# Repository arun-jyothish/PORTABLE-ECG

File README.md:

# PORTABLE-ECG
A Handheld ECG Machine with Mobile phone and Laptop interface. Cardiac condition prediction using ML

[jump to README 2](src/README.md)

[variable link][var link]
LOCK

[var link]: https://GOOGLE.COM 

|part name|LCSC PART NO|LINK|
|-----|-----|----|
|OLED| 	C2890600|https://lcsc.com/product-detail/span-style-background-color-ff0-OLED-span-Displays-Modules_Shenzhen-Allvision-Tech-N096-2864TMBEG0-H30_C2890600.html|
|RESISTOR|
|CAPACITOR|
|TYPEC CONN|
hello world
<br>

[![Contributors][Contributors-shield]][Contributors-url]

<br>

## P-ECG MACHINE

In the prediction feature, patient's ECG signal is compared with various cardio gram.
as the processing result the machine filter out many heart disease and predicts the most probable disease that should affect the person's life'

## BLOCK DIAGRAM
~~~mermaid

graph TD
 
    UART-->PWR
    PWR[USB PORT]-->CHR[CHARGING CIRCUIT]
    CHR-->BAT[BATTERY 3.7 LI-ION]
    RGL[POWER REGULATOR]-.->|3.3 VOLT|OLED[OLED 128*64]
    CHR-->RGL
    BAT-->RGL
    RGL-.->|3.7 VOLT|UC 
    UC{MICROCONTROLLER}-->OLED
   
    UC-->UART[USB TO TTL CONVERTER]
    PWR-.->EXT[COMPUTER]
    PWR-.->EXT2[MOBILE]
    probe[/PROBE/]-->|DATA|INS
    RGL-.->INS
    RA((RA))-->probe
    RL((RL))-->probe
    LA((LA))-->probe
    INS[INSTRUMENTATION AMPLIFIER] --->|ANALOG DATA| UC
~~~

~~~mermaid
graph TD 

   I((IDEATION)) --> Q[PREPARE FAQ] 
    I --> D[CONSTRAINTS IN NEW IMPLEMENTATION]
    D-->M[ MEASURES TAKEN ]
    EX[IDENTIFYING EXISTING TECHNOLOGY]-->I
    FL[IDENTIFYING LIMITATIONS]-->I
    
~~~
~~~mermaid
graph TD
    H[COMPONENTS SELECTION]-->SCH[PREPARE SCHEMATICS]
    SCH-->PCB[DESIGN PCB LAYOUT]
   DSN[CHASY DESIGN]-->TST[TESTING STAGE]
    TST-.->|FAIL|SCH
    TST==>|SUCCESS|FINAL((PRODUCT))
    PCB-->DSN

~~~
[contributors-shield]: https://img.shields.io/github/contributors/Arun-jyothish/PORTABLE-ECG.svg?style=for-the-badge
[Contributors-url]:https://github.com/Arun-jyothish/PORTABLE-ECG/network/members

~~~mermaid

~~~

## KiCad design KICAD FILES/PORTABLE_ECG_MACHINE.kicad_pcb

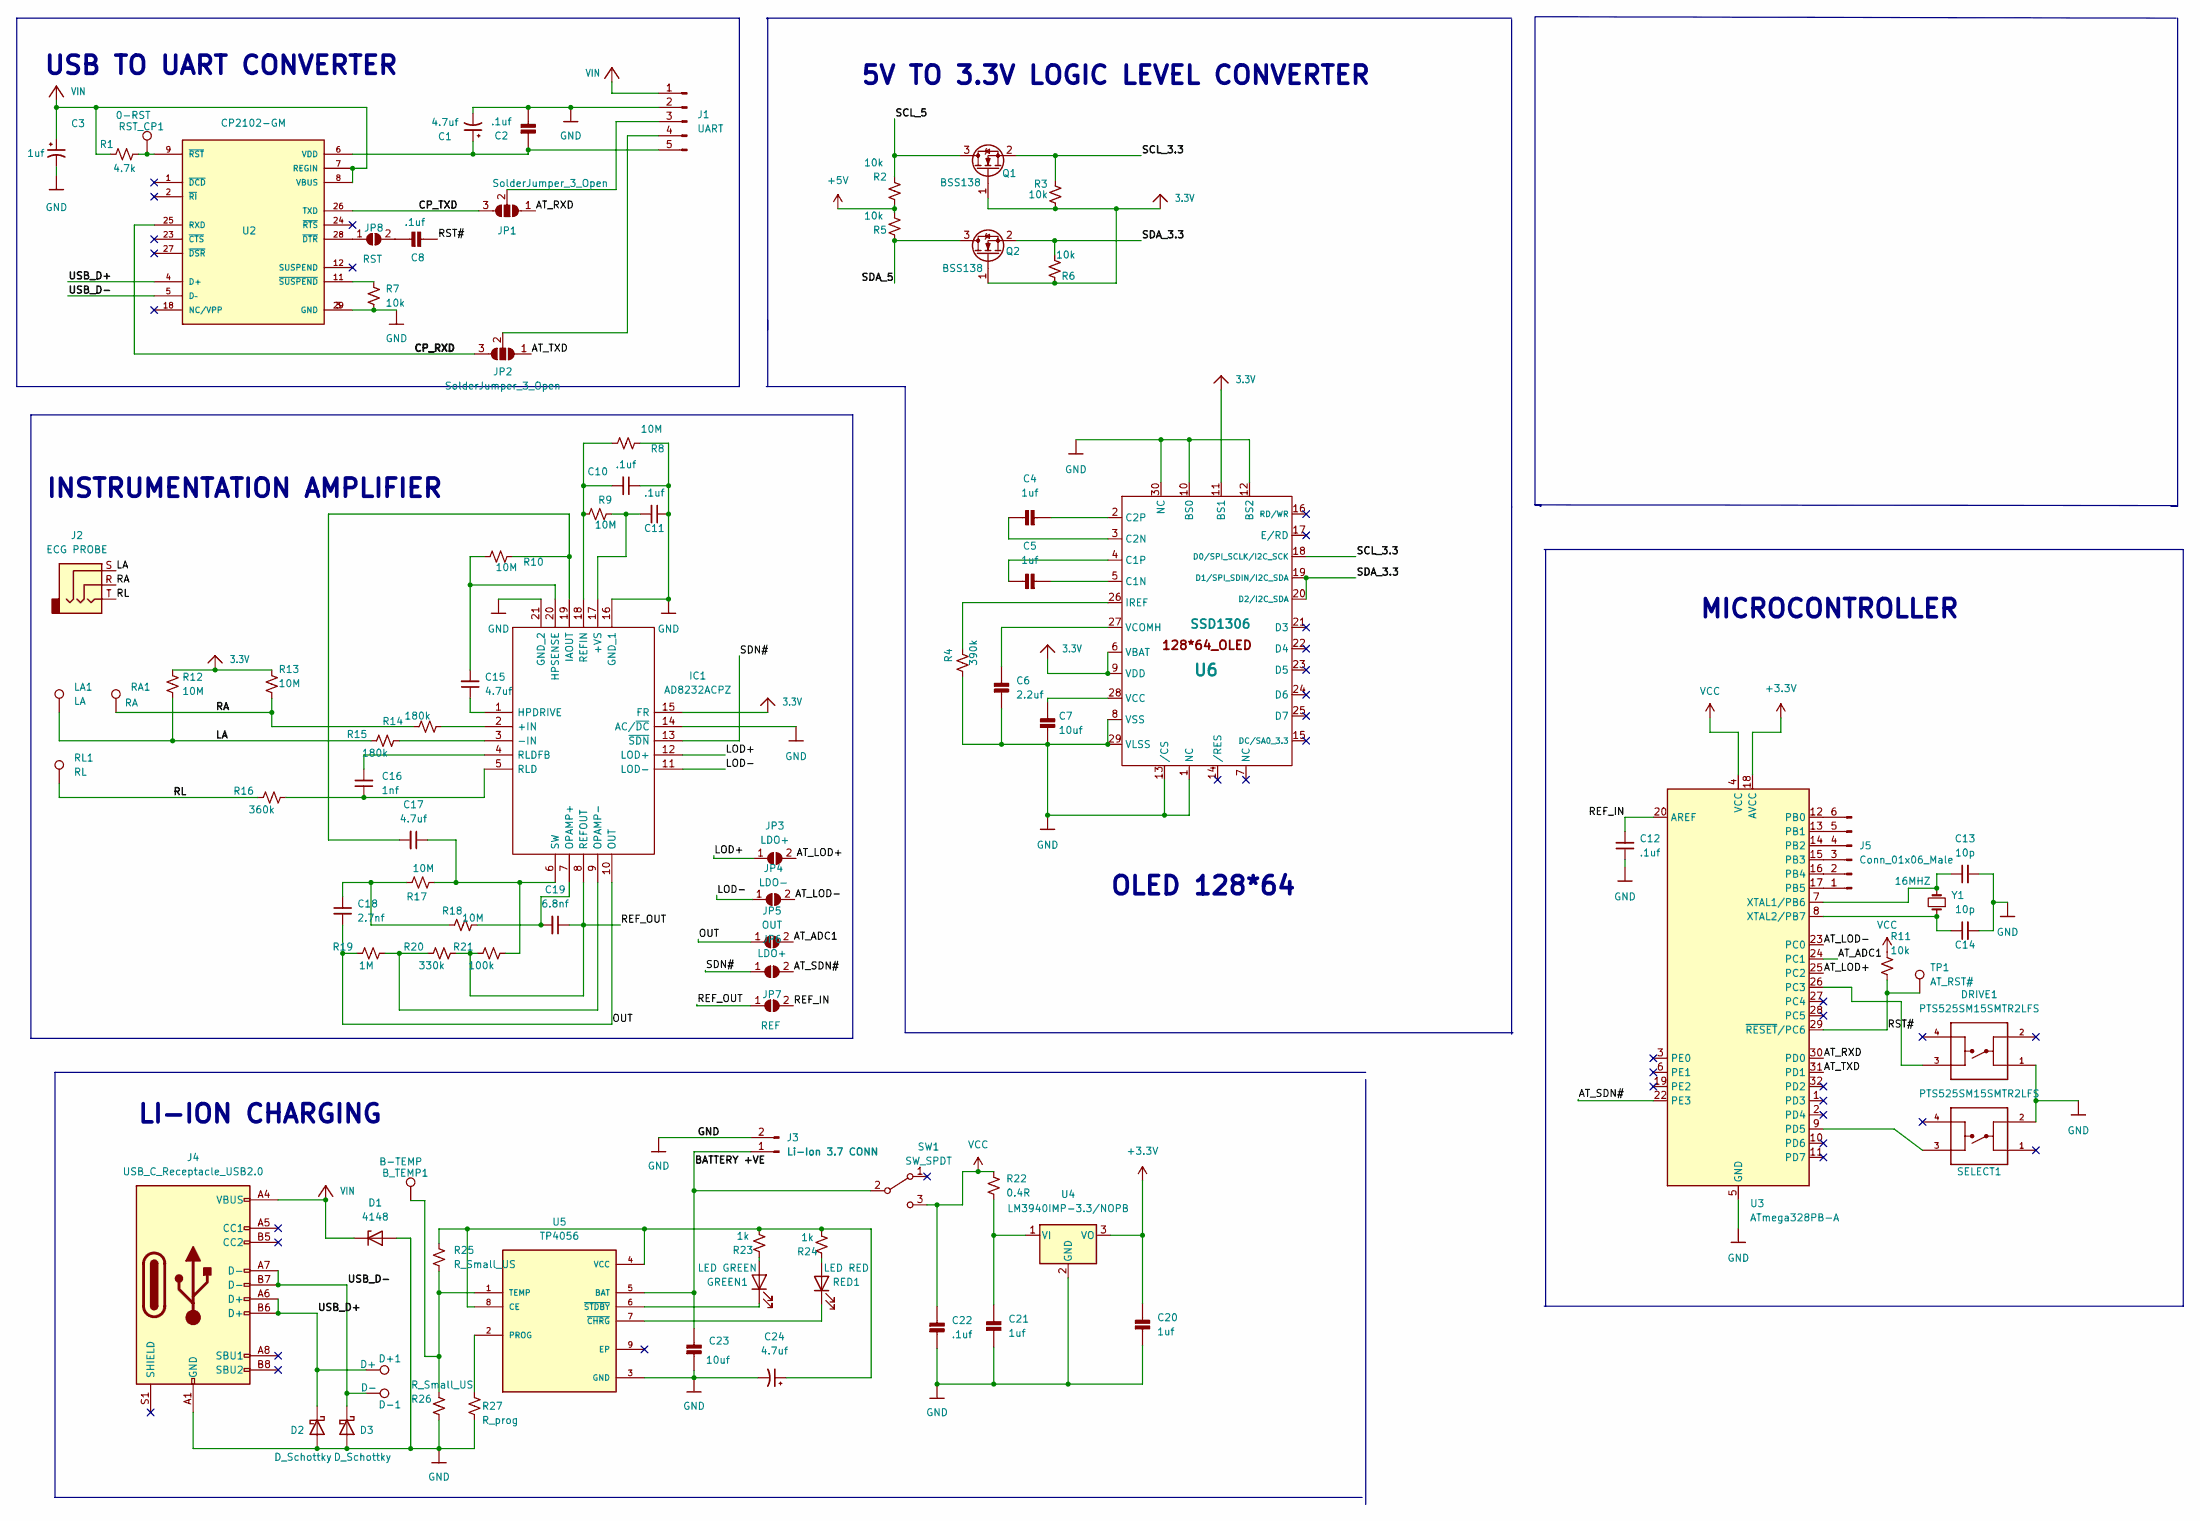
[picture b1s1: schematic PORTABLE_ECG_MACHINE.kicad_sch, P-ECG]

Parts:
B_TEMP1: B-TEMP; TestPoint_Pad_D1.0mm
C1, C15, C17, C24: 4.7uf; C_0603_1608Metric; JLC PCB PART NUMBER C2204347
C2, C8, C10, C11, C12, C22: .1uf; C_0603_1608Metric; JLC PCB PART NUMBER C2237744
C3, C4, C5, C20, C21: 1uf; C_0603_1608Metric; JLC PCB PART NUMBER C2168630
C6: 2.2uf; C_0603_1608Metric; JLC PCB PART NUMBER C2858007
C7, C23: 10uf; C_0603_1608Metric; JLC PCB PART NUMBER C2167337
C13, C14: 10p; C_0603_1608Metric; JLC PCB PART NUMBER C2184695
C16: 1nf; C_0603_1608Metric; JLC PCB PART NUMBER C100040
C18: 2.7nf; C_0603_1608Metric; JLC PCB PART NUMBER C107085
C19: 6.8nf; C_0603_1608Metric; JLC PCB PART NUMBER C2185892
D1: 4148; D_0603_1608Metric; JLC PCB PART NUMBER C109002
D2, D3: D_Schottky; D_0603_1608Metric; JLC PCB PART NUMBER C143772
D+1: D+; TestPoint_Pad_D1.0mm
D-1: D-; TestPoint_Pad_D1.0mm
DRIVE1: PTS525SM15SMTR2LFS; SW_PTS525SM15SMTR2LFS; PARTREV NA; JLC PCB PART NUMBER C221856
GREEN1: LED GREEN; LED_0603_1608Metric; JLC PCB PART NUMBER C2917809
IC1: AD8232ACPZ; QFN50P400X400X80-21N-D; Manufacturer_Part_Number AD8232ACPZ; Mouser Part Number N/A
J1: UART; PinHeader_1x05_P1.00mm_Horizontal
J2: ECG PROBE; Jack_3.5mm_CUI_SJ-3524-SMT_Horizontal; JLC PCB PART NUMBER C2939151
J3: Li-Ion 3.7 CONN; PinHeader_1x02_P1.00mm_Horizontal
J4: USB_C_Receptacle_USB2.0; USB_C_Receptacle_HRO_TYPE-C-31-M-12; JLC PCB PART NUMBER C2927026
J5: Conn_01x06_Male; 6PIN_CONN
JP1, JP2: SolderJumper_3_Open; 3_PIN_SOLDER_JUMPER_SMD
JP3, JP6: LDO+; 2_PIN_SMD_SOLDER_JUMPER
JP4: LDO-; 2_PIN_SMD_SOLDER_JUMPER
JP5: OUT; 2_PIN_SMD_SOLDER_JUMPER
JP7: REF; 2_PIN_SMD_SOLDER_JUMPER
JP8: RST; 2_PIN_SMD_SOLDER_JUMPER
LA1: LA; TestPoint_Pad_D1.0mm
Q1, Q2: BSS138; SOT-23; JLC PCB PART NUMBER C549757
R1: 4.7k; R_0603_1608Metric; JLC PCB PART NUMBER C2907166
R2, R3, R5, R6, R7, R11: 10k; R_0603_1608Metric; JLC PCB PART NUMBER C2930027
R4: 390k; R_0603_1608Metric; JLC PCB PART NUMBER C304747
R8, R9, R10, R12, R13, R17, R18: 10M; R_0603_1608Metric; JLC PCB PART NUMBER C2907090
R14, R15: 180k; R_0603_1608Metric; JLC PCB PART NUMBER C2907090
R16: 360k; R_0603_1608Metric; JLC PCB PART NUMBER C2907090
R19: 1M; R_0603_1608Metric; JLC PCB PART NUMBER C2907115
R20: 330k; R_0603_1608Metric; JLC PCB PART NUMBER C2907151
R21: 100k; R_0603_1608Metric; JLC PCB PART NUMBER C328419
R22: 0.4R; R_0603_1608Metric; JLC PCB PART NUMBER C2907088
R23, R24: 1k; R_0603_1608Metric; JLC PCB PART NUMBER C2913953
R25, R26: R_Small_US; R_0603_1608Metric
R27: R_prog; R_0603_1608Metric
RA1: RA; TestPoint_Pad_D1.0mm
RED1: LED RED; LED_0603_1608Metric; JLC PCB PART NUMBER C2917808
RL1: RL; TestPoint_Pad_D1.0mm
RST_CP1: 0-RST; TestPoint_Pad_D1.0mm
SELECT1: PTS525SM15SMTR2LFS; SW_PTS525SM15SMTR2LFS; PARTREV NA; JLC PCB PART NUMBER C221856
SW1: SW_SPDT; SW_SPDT_PCM12; JLC PCB PART NUMBER C2890358
TP1: AT_RST#; TestPoint_Pad_D1.0mm
U2: CP2102-GM; QFN50P500X500X100-29N; PARTREV 1.8; JLC PCB PART NUMBER C6568
U3: ATmega328PB-A; TQFP-32_7x7mm_P0.8mm; JLC PCB PART NUMBER C194192
U4: LM3940IMP-3.3/NOPB; SOT-223; JLC PCB PART NUMBER C140319
U5: TP4056; SOP127P600X175-9N; JLC PCB PART NUMBER C725790
U6: SSD1306; OLED-128O064D; JLC PCB PART NUMBER C2890600
Y1: 16MHZ; Crystal_SMD_0603-2Pin_6.0x3.5mm; JLC PCB PART NUMBER C112972

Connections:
3.3V: IC1.15 (FR), Q1.1 (G), Q2.1 (G), R3.1, R6.1, R12.1, R13.1, U6.6 (VBAT), U6.9 (VDD), U6.11 (BS1)
+3V3: C20.1, U3.18 (AVCC), U4.3 (VO)
+5V: R2.1, R5.2
/AT_ADC1: JP5.2 (B), U3.24 (PC1)
/AT_LOD+: JP3.2 (B), U3.25 (PC2)
/AT_LOD-: JP4.2 (B), U3.23 (PC0)
/AT_RXD: JP1.1 (A), U3.30 (PD0)
/AT_SDN#: JP6.2 (B), U3.22 (PE3)
/AT_TXD: JP2.1 (A), U3.31 (PD1)
/BATTERY +VE: C23.1, J3.1, SW1.2 (B), U5.5 (BAT)
/CP_RXD: JP2.3 (B), U2.25 (RXD)
/CP_TXD: JP1.3 (B), U2.26 (TXD)
/LA: J2.S, LA1.1, R12.2, R15.1
/LOD+: IC1.12 (LOD+), JP3.1 (A)
/LOD-: IC1.11 (LOD-), JP4.1 (A)
/OUT: C18.1, IC1.10 (OUT), JP5.1 (A), R19.1
/RA: J2.R, R13.2, R14.1, RA1.1
/REF_IN: C12.2, JP7.2 (B), U3.20 (AREF)
/REF_OUT: C19.1, IC1.8 (REFOUT), JP7.1 (A), R20.2, R21.1
/RL: J2.T, R16.1, RL1.1
/RST#: C8.2, R11.2, TP1.1, U3.29 (~RESET/PC6)
/SCL_3.3: Q1.2 (S), R3.2, U6.18 (D0/SPI_SCLK/I2C_SCK)
/SCL_5: Q1.3 (D), R2.2
/SDA_3.3: Q2.2 (S), R6.2, U6.19 (D1/SPI_SDIN/I2C_SDA), U6.20 (D2/I2C_SDA)
/SDA_5: Q2.3 (D), R5.1
/SDN#: IC1.13 (~SDN), JP6.1 (A)
/USB_D+: D2.1 (K), D+1.1, J4.A6 (D+), J4.B6 (D+), U2.4 (D+)
/USB_D-: D3.1 (K), D-1.1, J4.A7 (D-), J4.B7 (D-), U2.5 (D–)
GND: C1.2, C2.1, C3.2, C6.2, C7.2, C10.1, C11.1, C12.1, C13.2, C14.2, C20.2, C21.2, C22.2, C23.2, C24.2, D1.2 (A), D2.2 (A), D3.2 (A), DRIVE1.1, IC1.14 (AC/~DC), IC1.16 (GND_1), IC1.21 (GND_2), J1.2, J3.2, J4.A1 (GND), J4.A12 (GND), J4.B1 (GND), J4.B12 (GND), R4.2, R7.2, R8.1, R26.1, R27.1, SELECT1.2, U2.3 (GND), U2.29 (GND), U3.5 (GND), U3.21 (GND), U4.2 (GND), U5.3 (GND), U6.1 (NC), U6.8 (VSS), U6.10 (BS0), U6.12 (BS2), U6.13 (/CS), U6.29 (VLSS), U6.30 (NC)
unnamed: B_TEMP1.1, R25.2, R26.2, U5.1 (TEMP)
unnamed: C1.1, C2.2, J1.5, U2.6 (VDD)
unnamed: C4.1, U6.3 (C2N)
unnamed: C4.2, U6.2 (C2P)
unnamed: C5.1, U6.4 (C1P)
unnamed: C5.2, U6.5 (C1N)
unnamed: C6.1, U6.27 (VCOMH)
unnamed: C7.1, U6.28 (VCC)
unnamed: C8.1, JP8.2 (B)
unnamed: C10.2, IC1.18 (REFIN), R8.2, R9.2
unnamed: C11.2, IC1.17 (+VS), R9.1
unnamed: C13.1, U3.7 (XTAL1/PB6), Y1.2
unnamed: C14.1, U3.8 (XTAL2/PB7), Y1.1
unnamed: C15.1, IC1.1 (HPDRIVE)
unnamed: C15.2, IC1.20 (HPSENSE), R10.2
unnamed: C16.1, IC1.5 (RLD), R16.2
unnamed: C16.2, IC1.4 (RLDFB)
unnamed: C17.1, IC1.6 (SW), R17.2, R21.2
unnamed: C17.2, IC1.19 (IAOUT), R10.1
unnamed: C18.2, R17.1, R18.1
unnamed: C19.2, IC1.7 (OPAMP+), R18.2
unnamed: C21.1, R22.2, U4.1 (VI)
unnamed: C24.1, R23.2, R24.2, R25.1, U5.4 (VCC), U5.8 (CE)
unnamed: DRIVE1.3, U3.26 (PC3)
unnamed: GREEN1.1 (K), U5.6 (~STDBY)
unnamed: GREEN1.2 (A), R23.1
unnamed: IC1.2 (+IN), R14.2
unnamed: IC1.3 (-IN), R15.2
unnamed: IC1.9 (OPAMP-), R19.2, R20.1
unnamed: J1.3, JP1.2 (C)
unnamed: J1.4, JP2.2 (C)
unnamed: J5.1, U3.17 (PB5)
unnamed: J5.2, U3.16 (PB4)
unnamed: J5.3, U3.15 (PB3)
unnamed: J5.4, U3.14 (PB2)
unnamed: J5.5, U3.13 (PB1)
unnamed: J5.6, U3.12 (PB0)
unnamed: R1.2, RST_CP1.1, U2.9 (~RST)
unnamed: R4.1, U6.26 (IREF)
unnamed: R7.1, U2.11 (~SUSPEND)
unnamed: R24.1, RED1.2 (A)
unnamed: R27.2, U5.2 (PROG)
unnamed: RED1.1 (K), U5.7 (~CHRG)
unnamed: SELECT1.3, U3.9 (PD5)
unnamed: JP8.1 (A), U2.28 (~DTR)
VCC: C22.1, R11.1, R22.1, SW1.3 (C), U3.4 (VCC)
VIN: C3.1, D1.1 (K), J1.1, J4.A4 (VBUS), J4.A9 (VBUS), J4.B4 (VBUS), J4.B9 (VBUS), R1.1, U2.7 (REGIN), U2.8 (VBUS)

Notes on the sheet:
USB TO UART CONVERTER
INSTRUMENTATION AMPLIFIER
MICROCONTROLLER
OLED 128*64
LI-ION CHARGING
5V TO 3.3V LOGIC LEVEL CONVERTER

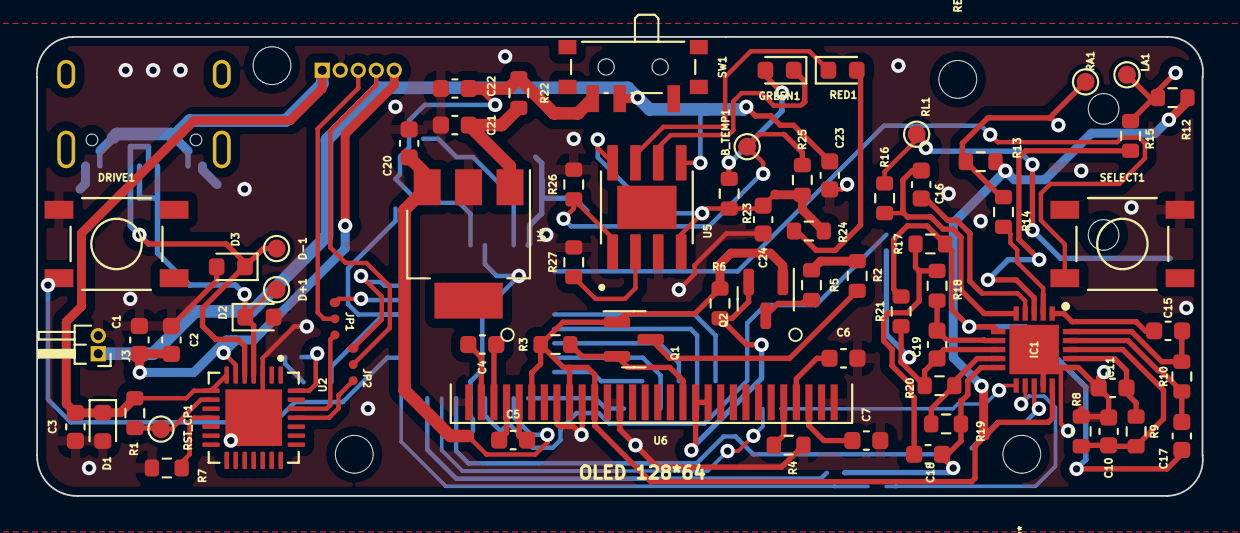
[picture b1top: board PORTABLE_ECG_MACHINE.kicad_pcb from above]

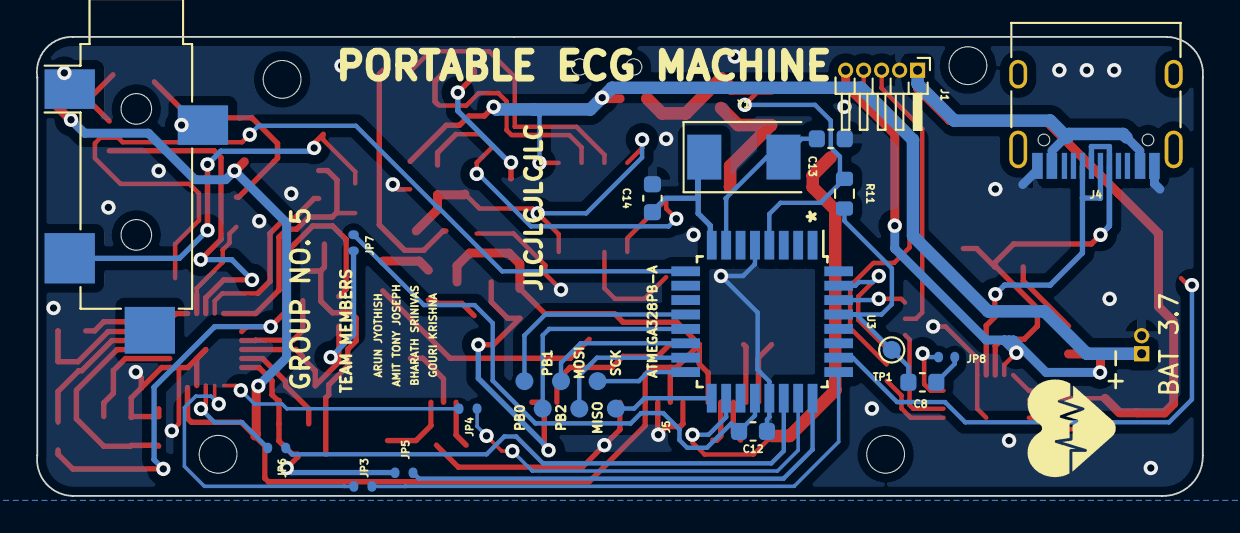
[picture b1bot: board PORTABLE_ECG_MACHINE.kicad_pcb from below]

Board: 2 copper layers, 64.8 x 25.5 mm, 88 parts (18 on the bottom side), 76 nets.

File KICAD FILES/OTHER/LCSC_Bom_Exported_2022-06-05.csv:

"LCSC Part Number","Package","Value","Quoted Manufacturer","Quoted LCSC Part Number","Quantity","Unit Price","Order Price","Quantity Available","Min\Mult Order Qty","RoHS","Part Match Confidence"
"C2204347","Capacitor_SMD:C_0603_1608Metric","4.7uf","AVX","C2204347","1","","0.01","","1\1","yes","100%"
"C2184695","Capacitor_SMD:C_0603_1608Metric","10p","KEMET","C2184695","1","","0.01","","1\1","yes","100%"
"C100040","Capacitor_SMD:C_0603_1608Metric","1nf","YAGEO","C100040","100","0.0026","0.26","8197500","100\100","yes","100%"
"C107085","Capacitor_SMD:C_0603_1608Metric","2.7nf","YAGEO","C107085","100","0.0036","0.36","1100","100\100","yes","100%"
"C2185892","Capacitor_SMD:C_0603_1608Metric","6.8nf","Vishay Intertech","C2185892","1","","0.01","","1\1","yes","100%"
"C2237744","Capacitor_SMD:C_0603_1608Metric",".1uf","AVX","C2237744","1","","0","","1\1","yes","100%"
"C2168630","Capacitor_SMD:C_0603_1608Metric","1uf","KEMET","C2168630","1","","0.01","","1\1","yes","100%"
"C2858007","Capacitor_SMD:C_0603_1608Metric","2.2uf","Kyocera","C2858007","1","","0.01","","1\1","yes","100%"
"C2167337","Capacitor_SMD:C_0603_1608Metric","10uf","AVX","C2167337","1","","0.01","","1\1","yes","100%"
"C109002","Diode_SMD:D_0603_1608Metric","4148","LIZ Elec","C109002","20","","0.48","","20\20","yes","100%"
"C143772","Diode_SMD:D_0603_1608Metric","D_Schottky","AVX","C143772","5","0.1088","0.54","2740","5\5","yes","100%"
"C221856","tactile switch:SW_PTS525SM15SMTR2LFS","PTS525SM15SMTR2LFS","C&K","C221856","1","0.1383","0.14","6655","1\1","yes","100%"
"C2917809","LED_SMD:LED_0603_1608Metric","LED GREEN","PARALIGHT","C2917809","10","0.045","0.45","3760","10\10","yes","100%"
"C652575","KiCad:QFN50P400X400X80-21N-D","AD8232ACPZ","Analog Devices","C652575","1","","3.29","","1\1","yes","100%"
"C2939151","Connector_Audio:Jack_3.5mm_CUI_SJ-3524-SMT_Horizontal","ECG PROBE","HOOYA","C2939151","1","0.1687","0.17","494","1\1","yes","100%"
"C2927026","Connector_USB:USB_C_Receptacle_HRO_TYPE-C-31-M-12","USB_C_Receptacle_USB2.0","DEALON","C2927026","10","0.046","0.46","6380","10\10","yes","100%"
"C549757","Package_TO_SOT_SMD:SOT-23","BSS138","Nexperia","C549757","1","","0.3","","1\1","yes","100%"
"C2907166","Resistor_SMD:R_0603_1608Metric","4.7k","FOJAN","C2907166","100","0.0009","0.09","95000","100\100","yes","100%"
"C2907090","Resistor_SMD:R_0603_1608Metric","180k","FOJAN","C2907090","100","0.0009","0.09","32000","100\100","yes","100%"
"C2907090","Resistor_SMD:R_0603_1608Metric","360k","FOJAN","C2907090","100","0.0009","0.09","32000","100\100","yes","100%"
"C2907115","Resistor_SMD:R_0603_1608Metric","1M","FOJAN","C2907115","100","0.001","0.1","34400","100\100","yes","100%"
"C2930027","Resistor_SMD:R_0603_1608Metric","10k","FOJAN","C2930027","100","0.0009","0.09","1457500","100\100","yes","100%"
"C2907151","Resistor_SMD:R_0603_1608Metric","330k","FOJAN","C2907151","100","0.001","0.1","56400","100\100","yes","100%"
"C328419","Resistor_SMD:R_0603_1608Metric","100k","Resistor.Today","C328419","10","0.073","0.73","25140","10\10","yes","100%"
"C2907088","Resistor_SMD:R_0603_1608Metric","0.4R","FOJAN","C2907088","100","0.0009","0.09","394400","100\100","yes","100%"
"C2913953","Resistor_SMD:R_0603_1608Metric","1k","SANYEAR","C2913953","20","0.0247","0.49","1100","20\20","yes","100%"
"C304747","Resistor_SMD:R_0603_1608Metric","390k","FH(Guangdong Fenghua Advanced Tech)","C304747","100","0.001","0.1","8100","100\100","yes","100%"
"C2907090","Resistor_SMD:R_0603_1608Metric","10M","FOJAN","C2907090","100","0.0009","0.09","32000","100\100","yes","100%"
"C2917808","LED_SMD:LED_0603_1608Metric","LED RED","PARALIGHT","C2917808","10","0.045","0.45","2470","10\10","yes","100%"
"C2890358","Button_Switch_SMD:SW_SPDT_PCM12","SW_SPDT","G-Switch","C2890358","5","0.1077","0.54","20420","5\5","yes","100%"
"C6568","CP2102-GM:QFN50P500X500X100-29N","CP2102-GM","SILICON LABS","C6568","1","2.6833","2.68","21873","1\1","yes","100%"
"C194192","Package_QFP:TQFP-32_7x7mm_P0.8mm","ATmega328PB-A","Microchip Tech","C194192","1","","2.88","","1\1","yes","100%"
"C140319","Package_TO_SOT_SMD:SOT-223","LM3940IMP-3.3/NOPB","Texas Instruments","C140319","1","1.4084","1.41","1672","1\1","yes","100%"
"C725790","tp4056 ftprnt:SOP127P600X175-9N","TP4056","UMW(Youtai Semiconductor Co., Ltd.)","C725790","1","0.1348","0.13","23205","1\1","yes","100%"
"C2890600","Display:OLED-128O064D","SSD1306","Shenzhen Allvision Tech","C2890600","1","3.4696","3.47","53","1\1","yes","100%"
"C112972","Crystal:Crystal_SMD_0603-2Pin_6.0x3.5mm","16MHZ","Yangxing Tech","C112972","5","0.0904","0.45","13570","5\5","yes","100%"

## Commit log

2022-05-17 schema update | datasheet & ref add | pcbnew initiate
2022-05-17 OLED-INSTR_AMP-LION_CHAR-UART EESCHEMA UPDATE | PCBNEW ROUGH ARANGE
2022-05-17 PCBNEW ROUGH STRUCTURE | EDGECUT PR
2022-05-17 PCBNEW edgecut update| compact rough design
2022-05-17 Fill Zone add | Edgecut complete
2022-05-18 PCBNEW LAYOUT FIX | ADD LIPO-USB_CONN-AUDIO_JACK-TACTILE SWITCH
2022-05-18 DRC CHECK
2022-05-19 OLED 3D change | uC add | .step gen v4
2022-05-19 Conn complete | DRC CHECK2 | TEST INITIATE #V6#
2022-05-19 F.SILK AND B.SILK -- FONT FIX | LAYOUT FIX
2022-05-19 CUSTOM PAD ADD | ANNOTATION CONFLICT RECTIFY
2022-05-22 conn complete | solder jumper add
    pcbnew connection complete with respect to schematics, solder jumper add
2022-05-24 new revision initiate
2022-05-25 PECG DIR ADD
2022-05-26 git pull stash?
2022-05-26 OLED 128*64 EESCHEMA UPDATE
2022-05-27 version 2.0 | oled 128*64
    new version created substituted 128*64 instead of 128*64. EESCHEMA and PCBNEW completed. OLED 128*64 3D MODEL need to fix
2022-05-27 patch
2022-05-27 README TEST
2022-05-27 readme link test
2022-05-27 readme link
2022-05-27 readme link relative path
2022-05-27 README.md link test
2022-06-02 BOM-README update
2022-06-02 README update
2022-06-04 REV 3
    footprint change tp4056,add new 3d model oled 128*64,kicad render imgs add
2022-06-04 schematics update
2022-06-04 rev3 fab files, board pdf
2022-06-04 rev3 modfied
2022-07-06 add oled_code_pecg
2022-07-30 add src codes
    onebutton code update
2022-07-30 onebutton code rev1
2022-07-30 structured
2022-07-30 ESP8266WIFI LIB add
